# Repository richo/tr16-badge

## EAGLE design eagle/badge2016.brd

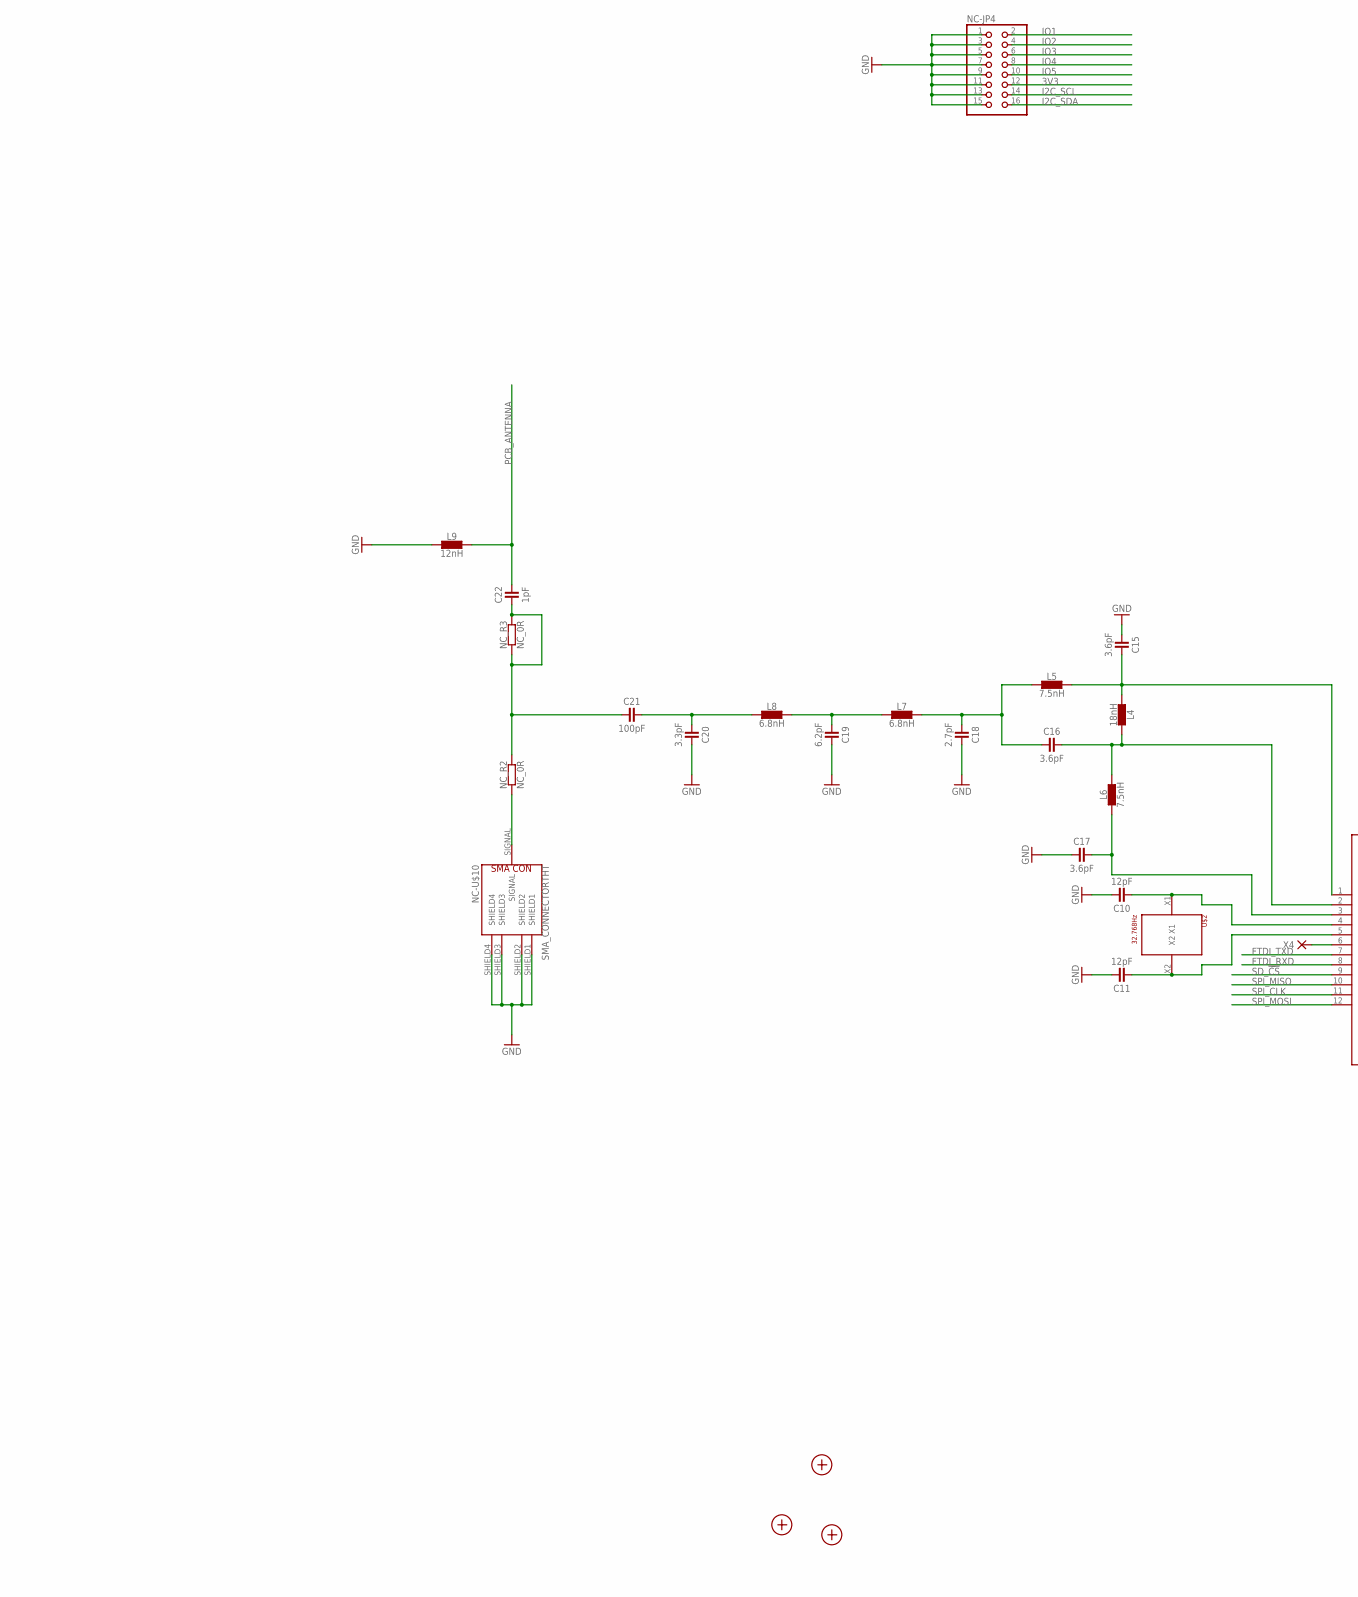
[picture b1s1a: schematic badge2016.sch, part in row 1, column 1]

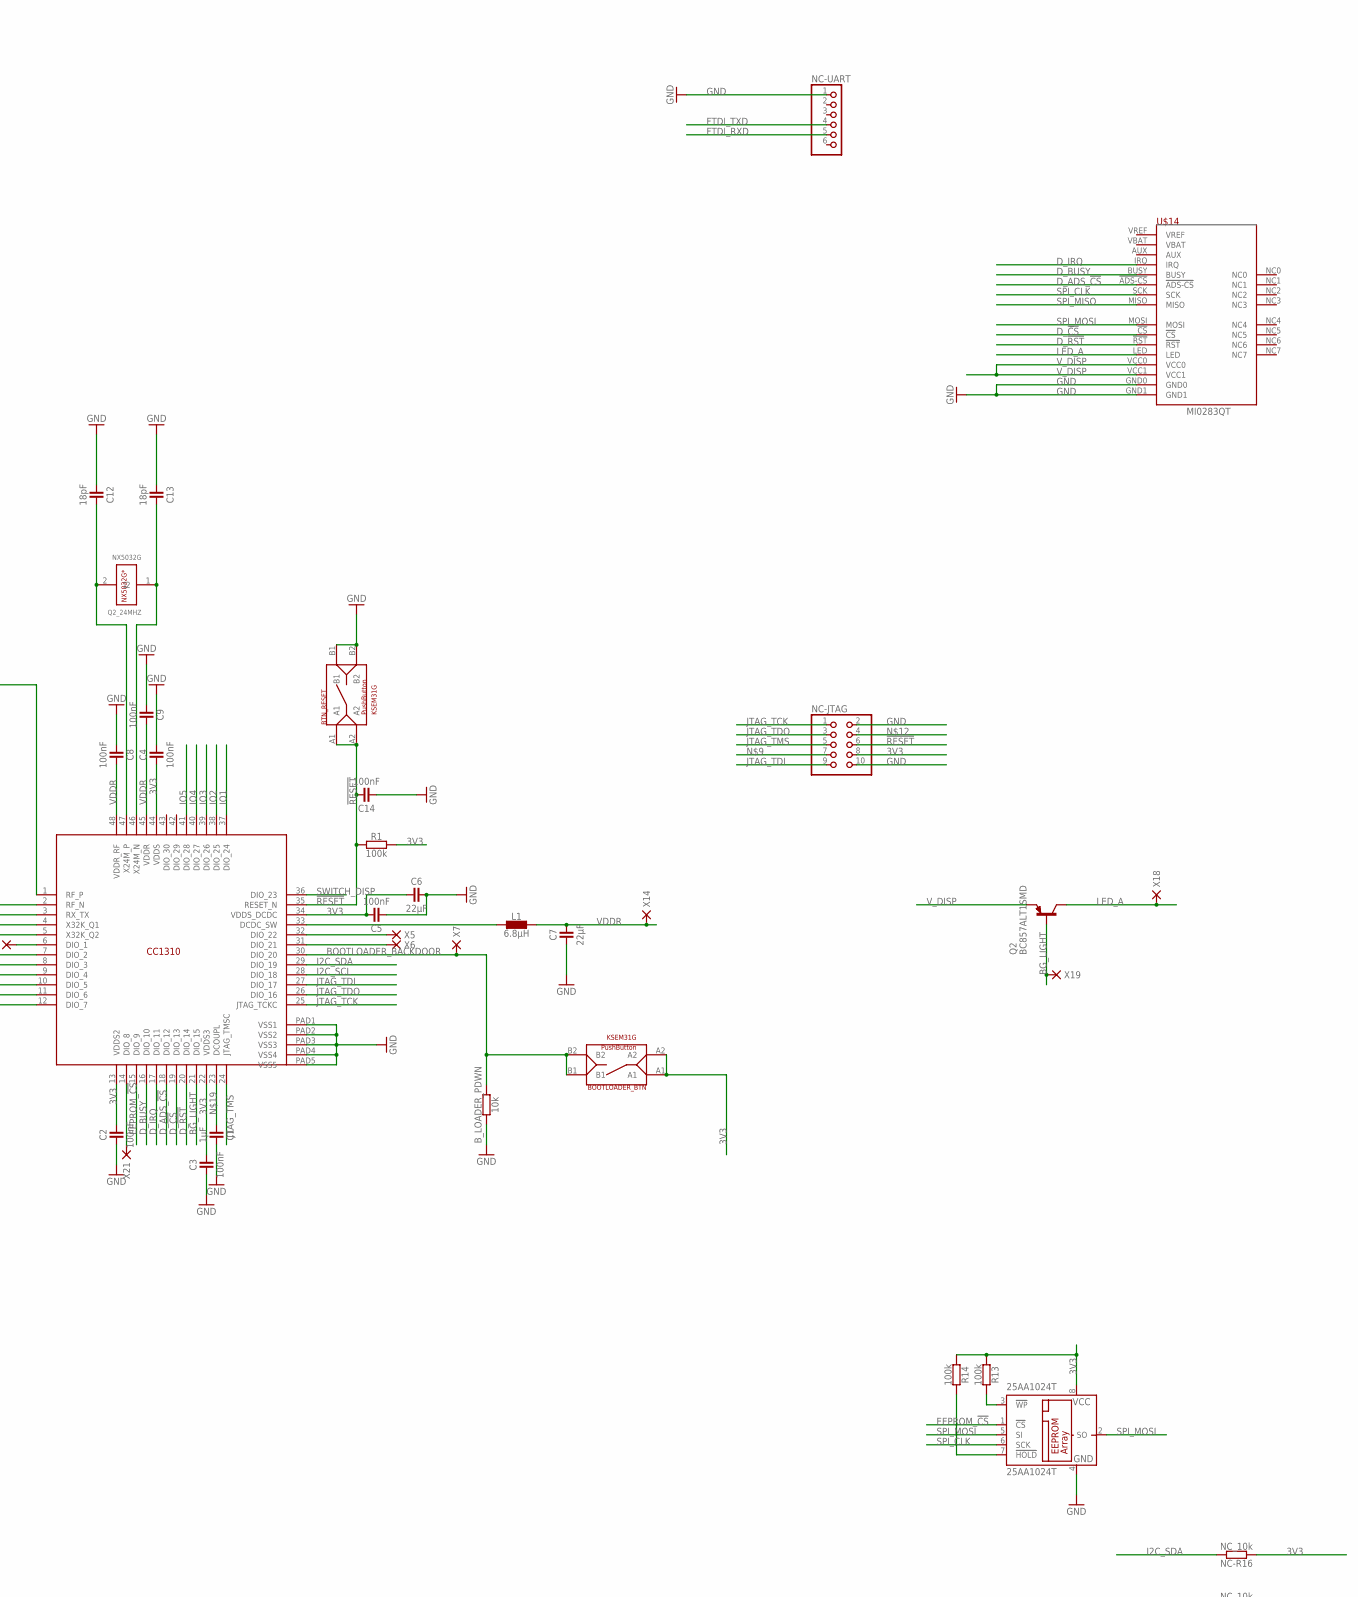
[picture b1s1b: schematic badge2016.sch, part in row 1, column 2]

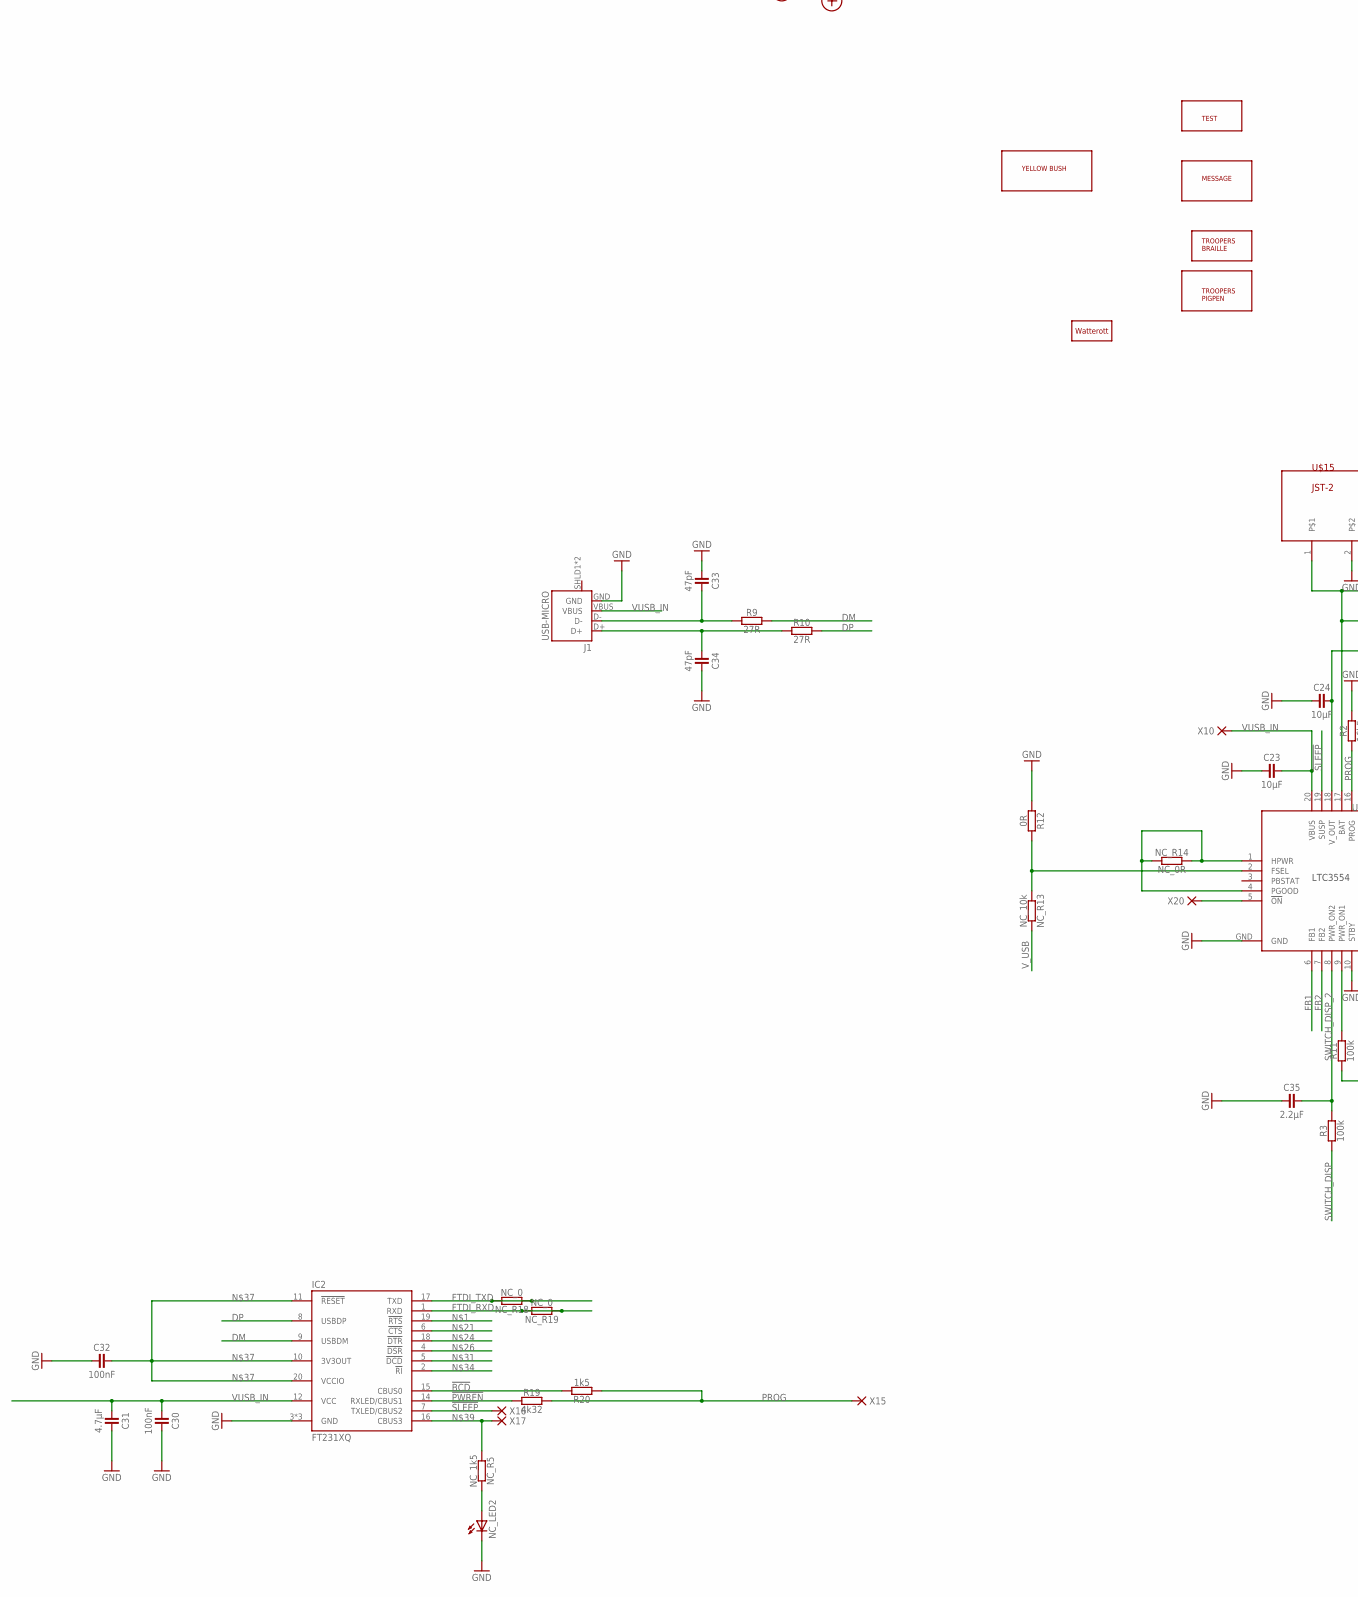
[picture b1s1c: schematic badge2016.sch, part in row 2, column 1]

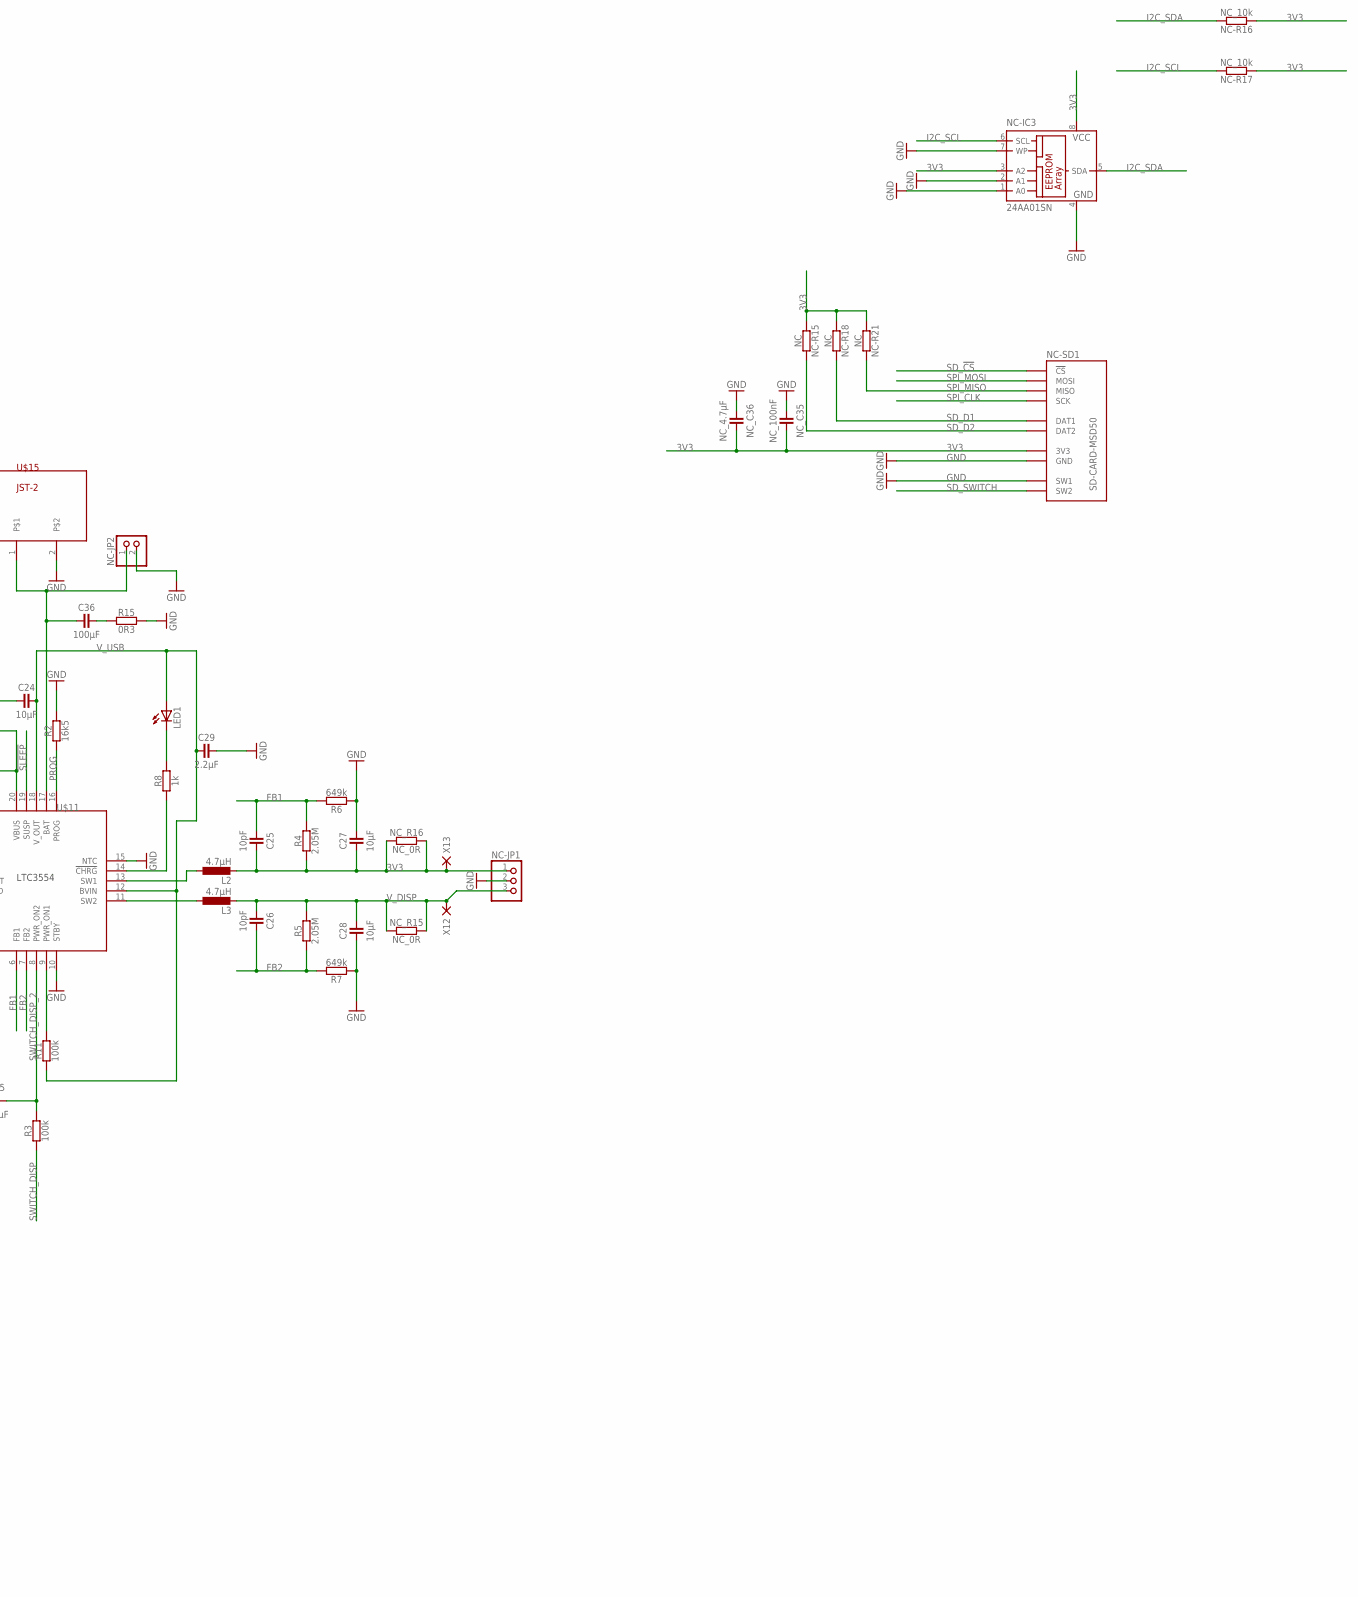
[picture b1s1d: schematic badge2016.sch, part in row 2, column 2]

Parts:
25AA1024T: 25AA1024T; SO-08
BOOTLOADER_BTN: KSEM31G
BTN_RESET: KSEM31G
B_LOADER_PDWN: 10k; C0402
C1: 1µF; C0402
C2, C3, C4, C5, C8, C9, C14, C30, C32: 100nF; C0402
C6, C7: 22µF; C0603
C10, C11: 12pF; C0402
C12, C13: 18pF; C0402
C15, C16, C17: 3.6pF; C0402
C18: 2.7pF; C0402
C19: 6.2pF; C0402
C20: 3.3pF; C0402
C21: 100pF; C0402
C22: 1pF; C0402
C23, C24, C27, C28: 10µF; C0805
C25, C26: 10pF; C0402
C29, C35: 2.2µF; C0603
C31: 4.7µF; C0402
C33, C34: 47pF; C0402
C36: 100µF; C1206
IC2: FT231XQ; QFN20-PAD
J1: USB-MICRO; USB-MICRO-10103594
L1: 6.8µH; C0603
L2, L3: 4.7µH; L1812
L4: 18nH; C0402
L5, L6: 7.5nH; C0402
L7, L8: 6.8nH; C0402
L9: 12nH; C0402
LED1: LED-0603; C0603
LOGO1: LOGO-S_LAYER; SPARK_TOP
NC-IC3: 24AA01SN; SO-08
NC-JP1: PINHD-1X3; 1X03
NC-JP2: PINHD-1X2; 1X02
NC-JP4: PINHD-2X8; 2X08
NC-JTAG: PINHD-2X5; 2X05
NC-R15, NC-R18, NC-R21: NC; C0402
NC-R16, NC-R17: NC_10k; C0402
NC-SD1: SD-CARD-MSD50; SD_5031821853
NC-U$10: SMA_CONNECTORTHT; SMA_CON_THT
NC-UART: PINHD-1X6; 1X06
NC_C35: NC_100nF; C0402
NC_C36: NC_4.7µF; C0402
NC_LED2: LED-0603; C0603
NC_R2, NC_R3, NC_R15, NC_R16: NC_0R; C0603
NC_R5: NC_1k5; C0402
NC_R13: NC_10k; C0402
NC_R14: NC_0R; C0402
NC_R18, NC_R19: NC_0; C0402
Q2: BC857ALT1SMD; SOT23-BEC
Q2_24MHZ: NX5032G; NX5032G*
R1, R3, R11, R13, R14: 100k; C0402
R2: 16k5; C0402
R4, R5: 2.05M; C0402
R6, R7: 649k; C0402
R8: 1k; C0402
R9, R10: 27R; C0402
R12: 0R; C0402
R15: 0R3; C0402
R19: 4k32; C0402
R20: 1k5; C0402
U$1: CC1310; S-PVQFN-N48
U$2: 32.768Hz; CMR200T
U$3: BB_TEST
U$4: MESSAGE
U$5: TR_BRAILLE
U$6: TR_PIGPEN
U$7: YELLOW_BUSH
U$11: LTC3554; QFN-20-3X3
U$14: MI0283QT
U$15: JST-2
X1, X2, X3: PASSER-07; PASSER_07MM
X4, X5, X6, X7, X21: PAD-0.5
X10, X12, X13, X14, X15, X16, X17, X18, X19, X20: PAD-1.27X1.27

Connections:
3V3: 25AA1024T.8 (VCC), BOOTLOADER_BTN.A1, BOOTLOADER_BTN.A2, C2.2, C3.2, C4.1, C5.2, C6.1, C25.2, C27.1, L2.2, NC-IC3.3 (A2), NC-IC3.8 (VCC), NC-JP1.1, NC-JP4.12, NC-JTAG.8, NC-R15.1, NC-R16.1, NC-R17.1, NC-R18.1, NC-R21.1, NC-SD1.VCC (3V3), NC_C35.2, NC_C36.2, NC_R16.1, NC_R16.2, R1.2, R4.1, R13.1, R14.1, U$1.13 (VDDS2), U$1.22 (VDDS3), U$1.34 (VDDS_DCDC), U$1.44 (VDDS), X13.1
!BCD: IC2.15 (CBUS0), R20.2
!PWREN: IC2.14 (RXLED/CBUS1), R19.1
!RESET: BTN_RESET.A1, BTN_RESET.A2, C14.2, NC-JTAG.6, R1.1, U$1.35 (RESET_N)
!SLEEP: IC2.7 (TXLED/CBUS2), U$11.19 (SUSP), X16.1
BG_LIGHT: Q2.B, U$1.21 (DIO_15), X19.1
BOOTLOADER_BACKDOOR: BOOTLOADER_BTN.B1, BOOTLOADER_BTN.B2, B_LOADER_PDWN.2, U$1.30 (DIO_20), X7.1
DM: IC2.9 (USBDM), R9.2
DP: IC2.8 (USBDP), R10.2
D_!CS: U$1.19 (DIO_13), U$14.!CS
D_!RST: U$1.20 (DIO_14), U$14.!RST
D_ADS_!CS: U$1.18 (DIO_12), U$14.!ADS-CS
D_BUSY: U$1.16 (DIO_10), U$14.BUSY
D_IRQ: U$1.17 (DIO_11), U$14.IRQ
EEPROM_!CS: 25AA1024T.1 (!CS), U$1.15 (DIO_9)
FB1: C25.1, R4.2, R6.2, U$11.6 (FB1)
FB2: C26.2, R5.1, R7.2, U$11.7 (FB2)
FTDI_RXD: IC2.1 (RXD), NC-UART.5, NC_R19.1, NC_R19.2, U$1.8 (DIO_3)
FTDI_TXD: IC2.17 (TXD), NC-UART.4, NC_R18.1, NC_R18.2, U$1.7 (DIO_2)
GND: 25AA1024T.4 (GND), BTN_RESET.B1, BTN_RESET.B2, B_LOADER_PDWN.1, C1.2, C2.1, C3.1, C4.2, C5.1, C6.2, C7.1, C8.1, C9.1, C10.2, C11.2, C12.1, C13.1, C14.1, C15.1, C17.1, C18.2, C19.2, C20.2, C23.1, C24.1, C27.2, C28.1, C29.2, C30.2, C31.2, C32.1, C33.1, C34.2, C35.1, IC2.3 (GND), IC2.13 (GND), IC2.TP (GND), J1.GND, L9.1, NC-IC3.1 (A0), NC-IC3.2 (A1), NC-IC3.4 (GND), NC-IC3.7 (WP), NC-JP1.2, NC-JP2.2, NC-JP4.1, NC-JP4.3, NC-JP4.5, NC-JP4.7, NC-JP4.9, NC-JP4.11, NC-JP4.13, NC-JP4.15, NC-JTAG.2, NC-JTAG.10, NC-SD1.GND, NC-SD1.SW1, NC-U$10.SHIELD1, NC-U$10.SHIELD2, NC-U$10.SHIELD3, NC-U$10.SHIELD4, NC-UART.1, NC_C35.1, NC_C36.1, NC_LED2.C, R2.2, R6.1, R7.1, R12.1, R15.2, U$1.PAD1 (VSS1), U$1.PAD2 (VSS2), U$1.PAD3 (VSS3), U$1.PAD4 (VSS4), U$1.PAD5 (VSS5), U$11.10 (STBY), U$11.15 (NTC), U$11.GND, U$14.GND0, U$14.GND1, U$15.2
I2C_SCL: NC-IC3.6 (SCL), NC-JP4.14, NC-R17.2, U$1.28 (DIO_18)
I2C_SDA: NC-IC3.5 (SDA), NC-JP4.16, NC-R16.2, U$1.29 (DIO_19)
IO1: NC-JP4.2, U$1.37 (DIO_24)
IO2: NC-JP4.4, U$1.38 (DIO_25)
IO3: NC-JP4.6, U$1.39 (DIO_26)
IO4: NC-JP4.8, U$1.40 (DIO_27)
IO5: NC-JP4.10, U$1.41 (DIO_28)
JTAG_TCK: NC-JTAG.1, U$1.25 (JTAG_TCKC)
JTAG_TDI: NC-JTAG.9, U$1.27 (DIO_17)
JTAG_TDO: NC-JTAG.3, U$1.26 (DIO_16)
JTAG_TMS: NC-JTAG.5, U$1.24 (JTAG_TMSC)
LED_A: Q2.C, U$14.LED, X18.1
unnamed: C10.1, U$1.4 (X32K_Q1), U$2.X1
unnamed: L1.1, U$1.33 (DCDC_SW)
unnamed: C12.2, Q2_24MHZ.2, U$1.47 (X24M_P)
unnamed: C13.2, Q2_24MHZ.1, U$1.46 (X24M_N)
unnamed: C16.2, L4.2, L6.2, U$1.2 (RF_N)
unnamed: C15.2, L4.1, L5.2, U$1.1 (RF_P)
unnamed: C16.1, C18.1, L5.1, L7.2
unnamed: C17.2, L6.1, U$1.3 (RX_TX)
unnamed: C19.1, L7.1, L8.2
unnamed: C20.1, C21.2, L8.1
unnamed: U$1.6 (DIO_1), X4.1
unnamed: C21.1, C22.1, NC_R2.2, NC_R3.1, NC_R3.2
unnamed: C11.1, U$1.5 (X32K_Q2), U$2.X2
unnamed: NC-U$10.SIGNAL, NC_R2.1
unnamed: L3.1, U$11.11 (SW2)
unnamed: C1.1, U$1.23 (DCOUPL)
unnamed: C36.1, NC-JP2.1, U$11.17 (BAT), U$15.1
unnamed: NC_R13.1, R12.2, U$11.2 (FSEL)
unnamed: L2.1, U$11.13 (SW1)
unnamed: C34.1, J1.D+, R10.1
unnamed: R8.1, U$11.14 (!CHRG)
unnamed: LED1.C, R8.2
unnamed: R11.2, U$11.9 (PWR_ON1)
unnamed: NC_R14.1, NC_R14.2, U$11.1 (HPWR), U$11.4 (PGOOD)
unnamed: C33.2, J1.D-, R9.1
unnamed: 25AA1024T.7 (!HOLD), R14.2
unnamed: U$1.32 (DIO_22), X5.1
unnamed: U$1.31 (DIO_21), X6.1
unnamed: C32.2, IC2.10 (3V3OUT), IC2.11 (!RESET), IC2.20 (VCCIO)
unnamed: 25AA1024T.3 (!WP), R13.2
unnamed: IC2.16 (CBUS3), NC_R5.1, X17.1
unnamed: NC_LED2.A, NC_R5.2
unnamed: U$11.5 (!ON), X20.1
unnamed: U$1.14 (DIO_8), X21.1
unnamed: C36.2, R15.1
PCB_ANTENNA: C22.2, L9.2
PROG: R2.1, R19.2, R20.1, U$11.16 (PROG), X15.1
SD_!CS: NC-SD1.CS (!CS), U$1.9 (DIO_4)
SD_D1: NC-R18.2, NC-SD1.DAT1
SD_D2: NC-R15.2, NC-SD1.DAT2
SD_SWITCH: NC-SD1.SW2
SPI_CLK: 25AA1024T.6 (SCK), NC-SD1.SCK, U$1.11 (DIO_6), U$14.SCK
SPI_MISO: NC-R21.2, NC-SD1.MISO, U$1.10 (DIO_5), U$14.MISO
SPI_MOSI: 25AA1024T.2 (SO), 25AA1024T.5 (SI), NC-SD1.MOSI, U$1.12 (DIO_7), U$14.MOSI
SWITCH_DISP: R3.1, U$1.36 (DIO_23)
SWITCH_DISP_2: C35.2, R3.2, U$11.8 (PWR_ON2)
VDDR: C7.2, C8.2, C9.2, L1.2, U$1.45 (VDDR), U$1.48 (VDDR_RF), X14.1
VUSB_IN: C23.2, C30.1, C31.1, IC2.12 (VCC), J1.VBUS, U$11.20 (VBUS), X10.1
V_DISP: C26.1, C28.2, L3.2, NC-JP1.3, NC_R15.1, NC_R15.2, Q2.E, R5.2, U$14.VCC0, U$14.VCC1, X12.1
V_USB: C24.2, C29.1, LED1.A, NC_R13.2, R11.1, U$11.12 (BVIN), U$11.18 (V_OUT)

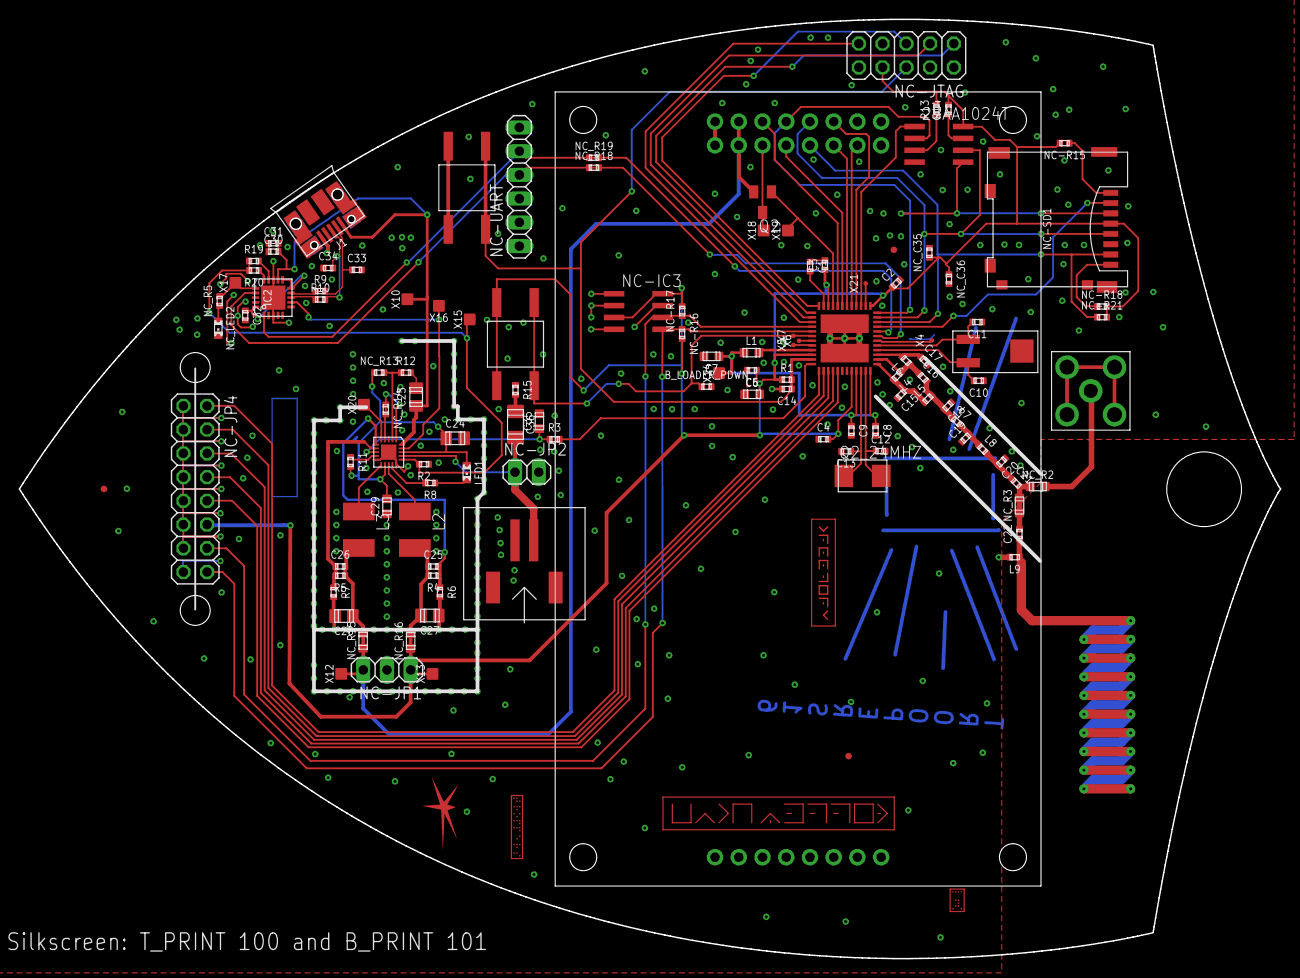
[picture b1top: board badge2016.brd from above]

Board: 2 copper layers, 135.0 x 100.5 mm, 125 parts (1 on the bottom side), 81 nets.

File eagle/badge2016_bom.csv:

Qty,Value,Device,Package,Parts,Description,DIGIKEY,MF,MPN,OC_FARNELL,OC_NEWARK
1,,LED-0603,C0603,LED1,LEDs,,,,,
1,0R,RESISTOR-0402,C0402,R12,Resistors,,,,,
1,0R3,RESISTOR-0402,C0402,R15,Resistors,,,,,
5,100k,RESISTOR-0402,C0402,"R1, R3, R11, R13, R14",Resistors,,,,,
9,100nF,CAPACITOR-0402,C0402,"C2, C3, C4, C5, C8, C9, C14, C30, C32",Capacitors,,,,,
1,100pF,CAPACITOR-0402,C0402,C21,Capacitors,,,,,
1,100µF,CAPACITOR-1206,C1206,C36,Capacitors,,,,,
1,10k,RESISTOR-0402,C0402,B_LOADER_PDWN,Resistors,,,,,
2,10pF,CAPACITOR-0402,C0402,"C25, C26",Capacitors,,,,,
4,10µF,CAPACITOR-0805,C0805,"C23, C24, C27, C28",Capacitors,,,,,
1,12nH,INDUCTOR-0402,C0402,L9,Inductors,,,,,
2,12pF,CAPACITOR-0402,C0402,"C10, C11",Capacitors,,,,,
1,16k5,RESISTOR-0402,C0402,R2,Resistors,,,,,
1,18nH,INDUCTOR-0402,C0402,L4,Inductors,,,,,
2,18pF,CAPACITOR-0402,C0402,"C12, C13",Capacitors,,,,,
1,1k,RESISTOR-0402,C0402,R8,Resistors,,,,,
1,1k5,RESISTOR-0402,C0402,R20,Resistors,,,,,
1,1pF,CAPACITOR-0402,C0402,C22,Capacitors,,,,,
1,1µF,CAPACITOR-0402,C0402,C1,Capacitors,,,,,
2,2.05M,RESISTOR-0402,C0402,"R4, R5",Resistors,,,,,
2,2.2µF,CAPACITOR-0603,C0603,"C29, C35",Capacitors,,,,,
1,2.7pF,CAPACITOR-0402,C0402,C18,Capacitors,,,,,
2,22µF,CAPACITOR-0603,C0603,"C6, C7",Capacitors,,,,,
1,25AA1024T,25AA080SN,SO-08,25AA1024T,"Serial EEPROM 4K/ 8K , SPI bus",,MICROCHIP,25AA080/SN,1816072,92C7351
2,27R,RESISTOR-0402,C0402,"R9, R10",Resistors,,,,,
1,3.3pF,CAPACITOR-0402,C0402,C20,Capacitors,,,,,
3,3.6pF,CAPACITOR-0402,C0402,"C15, C16, C17",Capacitors,,,,,
1,32.768Hz,CMR200T,CMR200T,U$2,,,,,,
1,4.7µF,CAPACITOR-0402,C0402,C31,Capacitors,,,,,
2,4.7µH,L-EUL1812,L1812,"L2, L3","INDUCTOR, European symbol",,,,,
2,47pF,CAPACITOR-0402,C0402,"C33, C34",Capacitors,,,,,
1,4k32,RESISTOR-0402,C0402,R19,Resistors,,,,,
1,6.2pF,CAPACITOR-0402,C0402,C19,Capacitors,,,,,
2,6.8nH,INDUCTOR-0402,C0402,"L7, L8",Inductors,,,,,
1,6.8µH,INDUCTOR-0603,C0603,L1,Inductors,,,,,
2,649k,RESISTOR-0402,C0402,"R6, R7",Resistors,,,,,
2,7.5nH,INDUCTOR-0402,C0402,"L5, L6",Inductors,,,,,
1,BC857ALT1SMD,BC857ALT1SMD,SOT23-BEC,Q2,PNP Transistror,,,,,
1,CC1310,CC1310,S-PVQFN-N48,U$1,,,,,,
1,FT231XQ,FT231XQ,QFN20-PAD,IC2,FTDI FT231X  USB to UART Bridge (5V tolerant inputs),768-1128-6-ND,,,,
1,JST-2,JST-2,JST-2,U$15,,,,,,
2,KSEM31G,KSEM31G,KSEM31G,"BOOTLOADER_BTN, BTN_RESET",,,,,,
1,LTC3554,LTC3554,QFN-20-3X3,U$11,,,,,,
1,MI0283QT,MI0283QT,MI0283QT,U$14,,,,,,
1,NX5032G,NX5032G,NX5032G*,Q2_24MHZ,,,,,,
1,USB-MICRO,USB-MICRO,USB-MICRO-10103594,J1,USB Connectors,609-4050-6-ND,,,,

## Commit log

2015-12-02 Update badge2016.sch
    Review and changes LTC3554:
    * Missing connecting Pin 9 (PWR_ON1) via R11 to Pin 18 (V_OUT) to activate SW1
    * Change R2 from 1.87k to 750 (for max. load of 1A)
    * PIN 15 (NTC) to GND, because NTC is not in use
2015-12-02 Update Layout changes by LTC3554 review
    Review and changes LTC3554:
    * Missing connecting Pin 9 (PWR_ON1) via R11 to Pin 18 (V_OUT) to activate SW1
    * Change R2 from 1.87k to 750 (for max. load of 1A)
    * PIN 15 (NTC) to GND, because NTC is not in use
2015-12-04 Committer: Stefan Kiese new file: bom/bom_20151125.ods new file: datasheets/cc1310.pdf new file: notes/badge_qs_stefan.txt
2015-12-08 new datasheets
2015-12-08 New Display New USB <-> Serial + Connection to Power Supply Chip Moved Power Supply Chip, UART und JTAG Headers Changed Expansion Header
2015-12-09 updated bom
2015-12-09 qs notes updated
2015-12-10 QA_sk done, updated SCH&&BRD
2015-12-15 fixed the inductor label (nF to nH) swapped 32khz crystal to different package + added package to lbr add pinhead to battery connector
2015-12-29 added openocd script for cc13xx
2015-12-30 added backup of ftdi config (dumped with ftx_prog
2016-01-12 add gitignore
2016-01-12 add example project; add ti-cc13xx libs; add ti-cc13xx lib-documentation
2016-01-12 add readme
2016-01-12 readme: ti-doc
2016-01-17 fixed PCB with design
2016-01-18 Update badge2016.sch
    Change RX <-> TX for UART
    Add additional "pad" for DIO_8
2016-01-18 Update badge2016.brd
    Change RX <-> TX for UART
    Add additional "pin" for DIO_8
2016-01-18 fixed serial lines optimized ground layer below cc1310 changed ltc footprint, less cream fixed missing v_usb line below usb socket
2016-01-21 fixes ski
2016-01-22 added temporary eagle files
2016-01-27 blindly add all tirtos project files
2016-02-19 newest pcb state
2016-02-19 ccfg
2016-02-20 modified: contiki (modified content, untracked content)
2016-02-20 contiki
2016-02-20 contiki, board.h modified
2016-02-20 add python-reqs, short building&flashing guide (readme.md)
2016-02-22 Add PWM to platform/tr16-badge/ Add examples/tr16-badge/ and enable backlight with pwm
2016-02-22 PWM support
2016-02-22 PWM fix pin naming
2016-02-22 PWM fix defines
2016-02-22 PWM add missing include
2016-02-22 Add ext-flash and spi modules Info: Code just imported from sensortag - not tested if working; compiling OK
2016-02-23 SPI Flash correct pins
2016-02-23 final pcb layout + schematic
2016-02-24 applied notes from watterott
2016-02-24 Final Badge!
2016-02-24 Fix boot loop from previousl contiki-main.c Fix incorrect and deleted GPIO pin definition for LCD backlight
2016-02-24 Add multi process and test action for backdoor key
2016-02-27 SPI EEPROM Datasheet
2016-02-28 final badge with fixes from watterott
2016-03-01 fixed final values in schematics: changed spi memory to 1M change loads of caps
2016-03-01 changed values of NC parts so that they'd appear in BOM added final BOM as sent to watterott
2016-03-03 fixed format specifies to remove warnings
2016-03-06 main: remove rf-init; constrained working tx-example
2016-03-08 cleanup
2016-03-08 send/recv
2016-03-09 somehow working rx-version
2016-03-10 add uart-receive process
2016-03-12 cleanup; flash-wrapper (ext-flash _not_ working)
2016-03-12 event rename
2016-03-12 main pin init
2016-03-12 dspl test
2016-03-12 display on/off for later use
2016-03-12 pktlen
2016-03-12 print msg
2016-03-12 fix rfc commands
2016-03-12 multiple attempst to get RSSI
2016-03-13 rssi display
2016-03-13 actually receive more than one packet
2016-03-13 add message storage
2016-03-13 provision
2016-03-13 provision script
2016-03-13 half agenda
2016-03-14 agenda w/o speakers
2016-03-14 include eeprom routines from master
2016-03-14 flash: working build
2016-03-14 clock
2016-03-15 is_faked toggle ident
2016-03-15 repeater setup
2016-03-15 "shfelul"
2016-03-15 force receive timeout and reinit
2016-03-15 print_clock
2016-03-15 prov
2016-03-15 Added parsing and processing of received messages.
2016-03-15 Changed an output text.
2016-03-15 writepageN
2016-03-15 write N
2016-03-15 game prov
2016-03-15 storage
2016-03-15 Changed output_arbitrary_msg to use stack and commented some debugs.
2016-03-15 smaller footprint
2016-03-15 not testet flash write provision
2016-03-15 bl bd
2016-03-15 sned/receive test
2016-03-15 no output on pending
2016-03-15 switch min/hour
2016-03-15 chknparse
2016-03-15 todo solve -function
2016-03-15 Fix: print slot only once.
2016-03-15 Additional tests (ascii only) for arbitrary text.
2016-03-16 added lcd drawing code
2016-03-16 usage samples
2016-03-16 Working python script for radio.
2016-03-16 removed debug print
2016-03-16 ncg: todo check-solution
2016-03-16 compiles
2016-03-16 rm system_process
2016-03-16 rm time
2016-03-16 Management -> Mgmt
2016-03-16 Timos scrolling text for agenda.
2016-03-16 use global text bg variable
2016-03-16 Timos impl of variable background color.
2016-03-16 receivelock
2016-03-16 rm string output
2016-03-16 added ftx-prog
2016-03-16 Add badgeName.h for personalize the badge
2016-03-16 Enable PWM - disable RX debug Messages
2016-03-16 RF + Display Functional
2016-03-16 Working State, RF + Display - NOT FINAL
2016-03-16 Revert "Enable PWM - disable RX debug Messages"
    This reverts commit 66b39521b0aa7a5a2549ed291dad87703d1b0193.
2016-03-16 fixed builds
2016-03-16 color changes
2016-03-16 Implementation of challenge.
2016-03-16 Fix: deactivating challenge.
2016-03-16 added multicolor support and conditional makefiles
2016-03-16 Modified some text (shown via uart).
2016-03-16 Some testcases for rf (more to come)
2016-03-16 Fix: fillScreen before new message.
2016-03-16 final display state
2016-03-16 final display stay
2016-03-16 Fix: endless loop. + some text formating for display. Please enter the commit message for your changes. Lines starting
2016-03-16 added provision file
2016-03-16 debug off
2016-03-16 Last fix.
2016-03-17 richo hax
